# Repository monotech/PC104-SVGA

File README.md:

Schematic based on Sergey Kiselev's ISA SVGA schematic. http://www.malinov.com/Home/sergeys-projects/isa-supervga

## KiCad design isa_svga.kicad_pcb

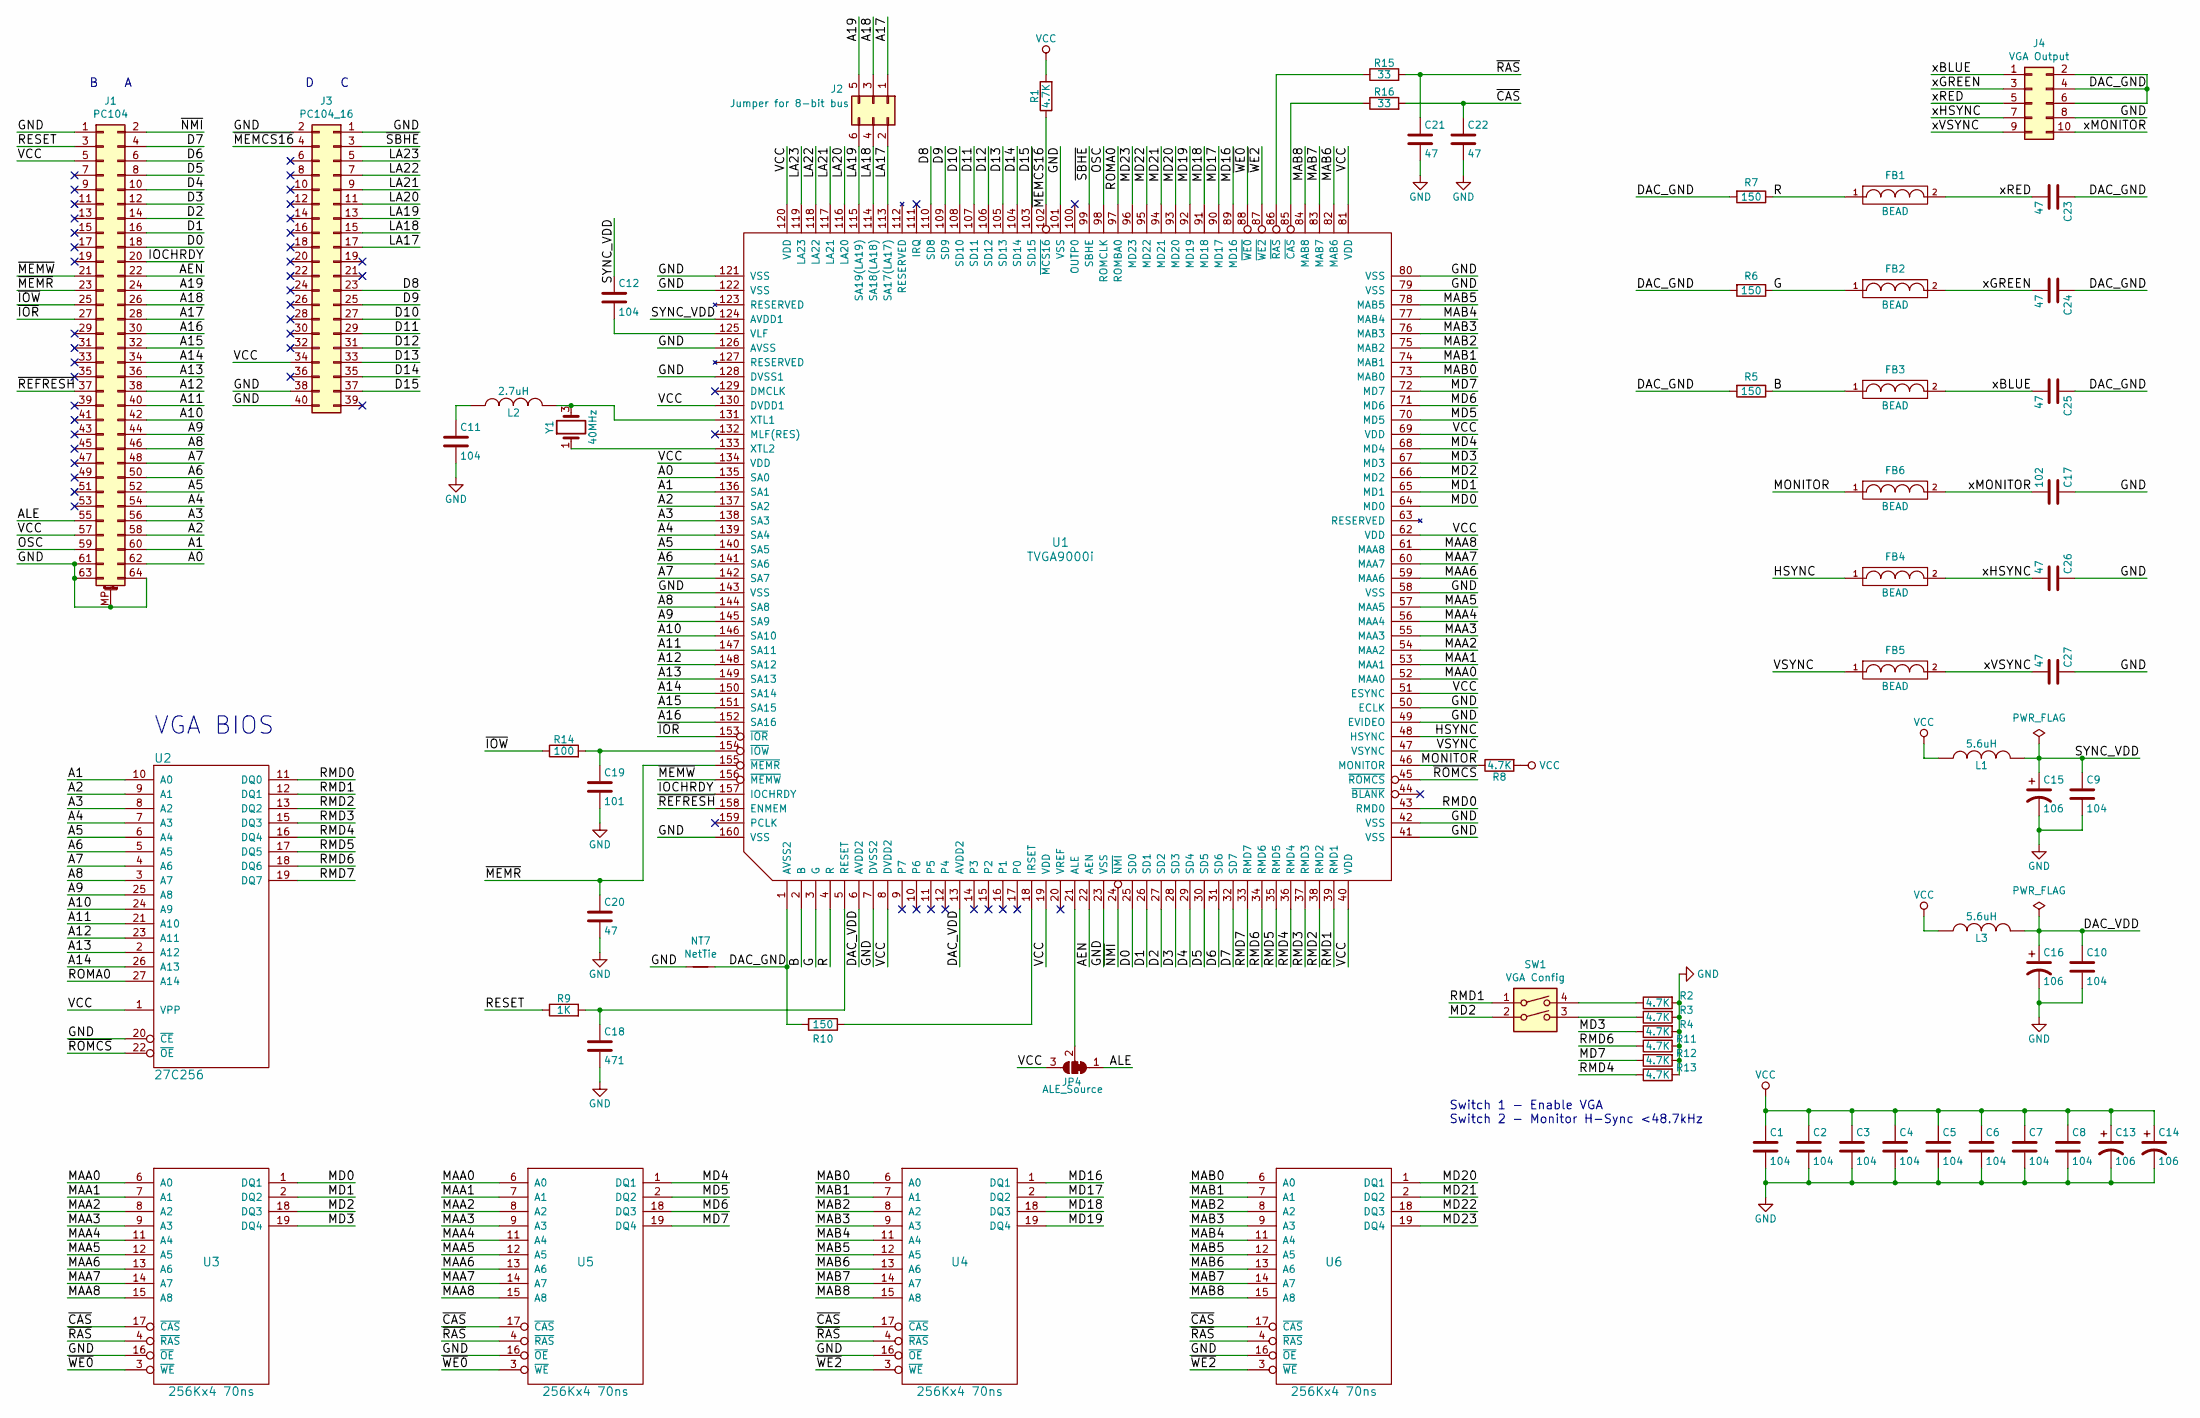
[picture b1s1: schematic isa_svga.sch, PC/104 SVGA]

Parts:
C1, C2, C3, C4, C5, C6, C7, C8, C9, C10, C11, C12: 104; C_0603_1608Metric
C13, C14, C15, C16: 106; C_0603_1608Metric
C17: 102; C_0805_2012Metric
C18: 471; C_0805_2012Metric
C19: 101; C_0805_2012Metric
C20, C21, C22, C23, C24, C25, C26, C27: 47; C_0603_1608Metric
FB1, FB2, FB3, FB4, FB5, FB6: BEAD; C_0805_2012Metric
J1: PC104; PC104_Platform
J2: Jumper for 8-bit bus; Triple-bridged-jumper
J3: PC104_16; PinSocket_2x20_P2.54mm_Vertical
J4: VGA Output; IDC-Header_2x05_P2.54mm_Horizontal
JP4: ALE_Source; SolderJumper-3_P1.3mm_Bridged12_Pad1.0x1.5mm
L1, L3: 5.6uH; C_0805_2012Metric
L2: 2.7uH; C_0805_2012Metric
NT7: NetTie; NetTie-2_SMD_Pad0.5mm
R1, R2, R3, R4, R8, R11, R12, R13: 4.7K; R_0805_2012Metric
R5, R6, R7, R10: 150; R_0805_2012Metric
R9: 1K; R_0805_2012Metric
R14: 100; R_0805_2012Metric
R15, R16: 33; R_0805_2012Metric
SW1: VGA Config; SW_DIP_SPSTx02_Slide_9.78x7.26mm_W7.62mm_P2.54mm
U1: TVGA9000i; PQFP-160_28x28mm_P0.65mm_LongPads
U2: 27C256; DIP-28_W15.24mm_Socket
U3, U4, U5, U6: 256Kx4 70ns; DIP-20_W7.62mm_Socket
Y1: 40MHz; Oscillator_SMD_Abracon_ASE-4Pin_3.2x2.5mm

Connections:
/A0: J1.62, U1.135 (SA0)
/A1: J1.60, U1.136 (SA1), U2.10 (A0)
/A2: J1.58, U1.137 (SA2), U2.9 (A1)
/A3: J1.56, U1.138 (SA3), U2.8 (A2)
/A4: J1.54, U1.139 (SA4), U2.7 (A3)
/A5: J1.52, U1.140 (SA5), U2.6 (A4)
/A6: J1.50, U1.141 (SA6), U2.5 (A5)
/A7: J1.48, U1.142 (SA7), U2.4 (A6)
/A8: J1.46, U1.144 (SA8), U2.3 (A7)
/A9: J1.44, U1.145 (SA9), U2.25 (A8)
/A10: J1.42, U1.146 (SA10), U2.24 (A9)
/A11: J1.40, U1.147 (SA11), U2.21 (A10)
/A12: J1.38, U1.148 (SA12), U2.23 (A11)
/A13: J1.36, U1.149 (SA13), U2.2 (A12)
/A14: J1.34, U1.150 (SA14), U2.26 (A13)
/A15: J1.32, U1.151 (SA15)
/A16: J1.30, U1.152 (SA16)
/A17: J1.28, J2.1
/A18: J1.26, J2.3
/A19: J1.24, J2.5
/AEN: J1.22, U1.22 (AEN)
/ALE: J1.55, JP4.1 (A)
/B: FB3.1, R5.1, U1.2 (B)
/D0: J1.18, U1.25 (SD0)
/D1: J1.16, U1.26 (SD1)
/D2: J1.14, U1.27 (SD2)
/D3: J1.12, U1.28 (SD3)
/D4: J1.10, U1.29 (SD4)
/D5: J1.8, U1.30 (SD5)
/D6: J1.6, U1.31 (SD6)
/D7: J1.4, U1.32 (SD7)
/D8: J3.23, U1.110 (SD8)
/D9: J3.25, U1.109 (SD9)
/D10: J3.27, U1.108 (SD10)
/D11: J3.29, U1.107 (SD11)
/D12: J3.31, U1.106 (SD12)
/D13: J3.33, U1.105 (SD13)
/D14: J3.35, U1.104 (SD14)
/D15: J3.37, U1.103 (SD15)
/DAC_GND: C23.1, C24.1, C25.1, J4.2, J4.4, J4.6, NT7.2, R5.2, R6.2, R7.2, R10.2, U1.1 (AVSS2)
/DAC_VDD: C10.1, C16.1, L3.2, U1.6 (AVDD2), U1.13 (AVDD2)
/G: FB2.1, R6.1, U1.3 (G)
/HSYNC: FB4.1, U1.48 (HSYNC)
/IOCHRDY: J1.20, U1.157 (IOCHRDY)
/LA17: J2.2, J3.17, U1.113 (SA17(LA17))
/LA18: J2.4, J3.15, U1.114 (SA18(LA18))
/LA19: J2.6, J3.13, U1.115 (SA19(LA19))
/LA20: J3.11, U1.116 (LA20)
/LA21: J3.9, U1.117 (LA21)
/LA22: J3.7, U1.118 (LA22)
/LA23: J3.5, U1.119 (LA23)
/MAA0: U1.52 (MAA0), U3.6 (A0), U5.6 (A0)
/MAA1: U1.53 (MAA1), U3.7 (A1), U5.7 (A1)
/MAA2: U1.54 (MAA2), U3.8 (A2), U5.8 (A2)
/MAA3: U1.55 (MAA3), U3.9 (A3), U5.9 (A3)
/MAA4: U1.56 (MAA4), U3.11 (A4), U5.11 (A4)
/MAA5: U1.57 (MAA5), U3.12 (A5), U5.12 (A5)
/MAA6: U1.59 (MAA6), U3.13 (A6), U5.13 (A6)
/MAA7: U1.60 (MAA7), U3.14 (A7), U5.14 (A7)
/MAA8: U1.61 (MAA8), U3.15 (A8), U5.15 (A8)
/MAB0: U1.73 (MAB0), U4.6 (A0), U6.6 (A0)
/MAB1: U1.74 (MAB1), U4.7 (A1), U6.7 (A1)
/MAB2: U1.75 (MAB2), U4.8 (A2), U6.8 (A2)
/MAB3: U1.76 (MAB3), U4.9 (A3), U6.9 (A3)
/MAB4: U1.77 (MAB4), U4.11 (A4), U6.11 (A4)
/MAB5: U1.78 (MAB5), U4.12 (A5), U6.12 (A5)
/MAB6: U1.82 (MAB6), U4.13 (A6), U6.13 (A6)
/MAB7: U1.83 (MAB7), U4.14 (A7), U6.14 (A7)
/MAB8: U1.84 (MAB8), U4.15 (A8), U6.15 (A8)
/MD0: U1.64 (MD0), U3.1 (DQ1)
/MD1: U1.65 (MD1), U3.2 (DQ2)
/MD2: SW1.2, U1.66 (MD2), U3.18 (DQ3)
/MD3: R4.1, U1.67 (MD3), U3.19 (DQ4)
/MD4: U1.68 (MD4), U5.1 (DQ1)
/MD5: U1.70 (MD5), U5.2 (DQ2)
/MD6: U1.71 (MD6), U5.18 (DQ3)
/MD7: R12.1, U1.72 (MD7), U5.19 (DQ4)
/MD16: U1.89 (MD16), U4.1 (DQ1)
/MD17: U1.90 (MD17), U4.2 (DQ2)
/MD18: U1.91 (MD18), U4.18 (DQ3)
/MD19: U1.92 (MD19), U4.19 (DQ4)
/MD20: U1.93 (MD20), U6.1 (DQ1)
/MD21: U1.94 (MD21), U6.2 (DQ2)
/MD22: U1.95 (MD22), U6.18 (DQ3)
/MD23: U1.96 (MD23), U6.19 (DQ4)
/MONITOR: FB6.1, R8.1, U1.46 (MONITOR)
/OSC: J1.59, U1.98 (ROMCLK)
/R: FB1.1, R7.1, U1.4 (R)
/RESET: J1.3, R9.1
/RMD0: U1.43 (RMD0), U2.11 (DQ0)
/RMD1: SW1.1, U1.39 (RMD1), U2.12 (DQ1)
/RMD2: U1.38 (RMD2), U2.13 (DQ2)
/RMD3: U1.37 (RMD3), U2.15 (DQ3)
/RMD4: R13.1, U1.36 (RMD4), U2.16 (DQ4)
/RMD5: U1.35 (RMD5), U2.17 (DQ5)
/RMD6: R11.1, U1.34 (RMD6), U2.18 (DQ6)
/RMD7: U1.33 (RMD7), U2.19 (DQ7)
/ROMA0: U1.97 (ROMBA0), U2.27 (A14)
/SYNC_VDD: C9.1, C12.1, C15.1, L1.2, U1.124 (AVDD1)
/VSYNC: FB5.1, U1.47 (VSYNC)
/xBLUE: C25.2, FB3.2, J4.1
/xGREEN: C24.2, FB2.2, J4.3
/xHSYNC: C26.2, FB4.2, J4.7
/xMONITOR: C17.2, FB6.2, J4.10
/xRED: C23.2, FB1.2, J4.5
/xVSYNC: C27.2, FB5.2, J4.9
/~CAS: C22.1, R16.2, U3.17 (~CAS), U4.17 (~CAS), U5.17 (~CAS), U6.17 (~CAS)
/~IOR: J1.27, U1.153 (~IOR)
/~IOW: J1.25, R14.1
/~MEMCS16: J3.4, R1.1, U1.102 (~MCS16)
/~MEMR: C20.1, J1.23, U1.155 (~MEMR)
/~MEMW: J1.21, U1.156 (~MEMW)
/~NMI: J1.2, U1.24 (~NMI)
/~RAS: C21.1, R15.2, U3.4 (~RAS), U4.4 (~RAS), U5.4 (~RAS), U6.4 (~RAS)
/~REFRESH: J1.37, U1.158 (ENMEM)
/~ROMCS: U1.45 (~ROMCS), U2.22 (~OE)
/~SBHE: J3.3, U1.99 (SBHE)
/~WE0: U1.88 (~WE0), U3.3 (~WE), U5.3 (~WE)
/~WE2: U1.87 (~WE2), U4.3 (~WE), U6.3 (~WE)
GND: C1.2, C2.2, C3.2, C4.2, C5.2, C6.2, C7.2, C8.2, C9.2, C10.2, C11.2, C13.2, C14.2, C15.2, C16.2, C17.1, C18.2, C19.2, C20.2, C21.2, C22.2, C26.1, C27.1, J1.1, J1.61, J1.63, J1.64, J1.MP (MountPin), J3.1, J3.2, J3.38, J3.40, J4.8, NT7.1, R2.2, R3.2, R4.2, R11.2, R12.2, R13.2, U1.7 (DVSS2), U1.23 (VSS), U1.41 (VSS), U1.42 (VSS), U1.49 (EVIDEO), U1.50 (ECLK), U1.58 (VSS), U1.79 (VSS), U1.80 (VSS), U1.101 (VSS), U1.121 (VSS), U1.122 (VSS), U1.126 (AVSS), U1.128 (DVSS1), U1.143 (VSS), U1.160 (VSS), U2.14 (GND), U2.20 (~CE), U3.16 (~OE), U3.20 (GND), U4.16 (~OE), U4.20 (GND), U5.16 (~OE), U5.20 (GND), U6.16 (~OE), U6.20 (GND)
unnamed: C11.1, L2.1
unnamed: C12.2, U1.125 (VLF)
unnamed: C18.1, R9.2, U1.5 (RESET)
unnamed: C19.1, R14.2, U1.154 (~IOW)
unnamed: JP4.2 (C), U1.21 (ALE)
unnamed: L2.2, U1.131 (XTL1), Y1.3
unnamed: R2.1, SW1.4
unnamed: R3.1, SW1.3
unnamed: R10.1, U1.18 (IRSET)
unnamed: R15.1, U1.86 (~RAS)
unnamed: R16.1, U1.85 (~CAS)
unnamed: U1.133 (XTL2), Y1.1
VCC: C1.1, C2.1, C3.1, C4.1, C5.1, C6.1, C7.1, C8.1, C13.1, C14.1, J1.5, J1.57, J3.34, JP4.3 (B), L1.1, L3.1, R1.2, R8.2, U1.8 (DVDD2), U1.19 (VDD), U1.40 (VDD), U1.51 (ESYNC), U1.62 (VDD), U1.69 (VDD), U1.81 (VDD), U1.120 (VDD), U1.130 (DVDD1), U1.134 (VDD), U2.1 (VPP), U2.28 (VCC), U3.10 (VCC), U4.10 (VCC), U5.10 (VCC), U6.10 (VCC)

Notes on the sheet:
VGA BIOS
Switch 1 - Enable VGA Switch 2 - Monitor H-Sync <48.7kHz
B A
D C

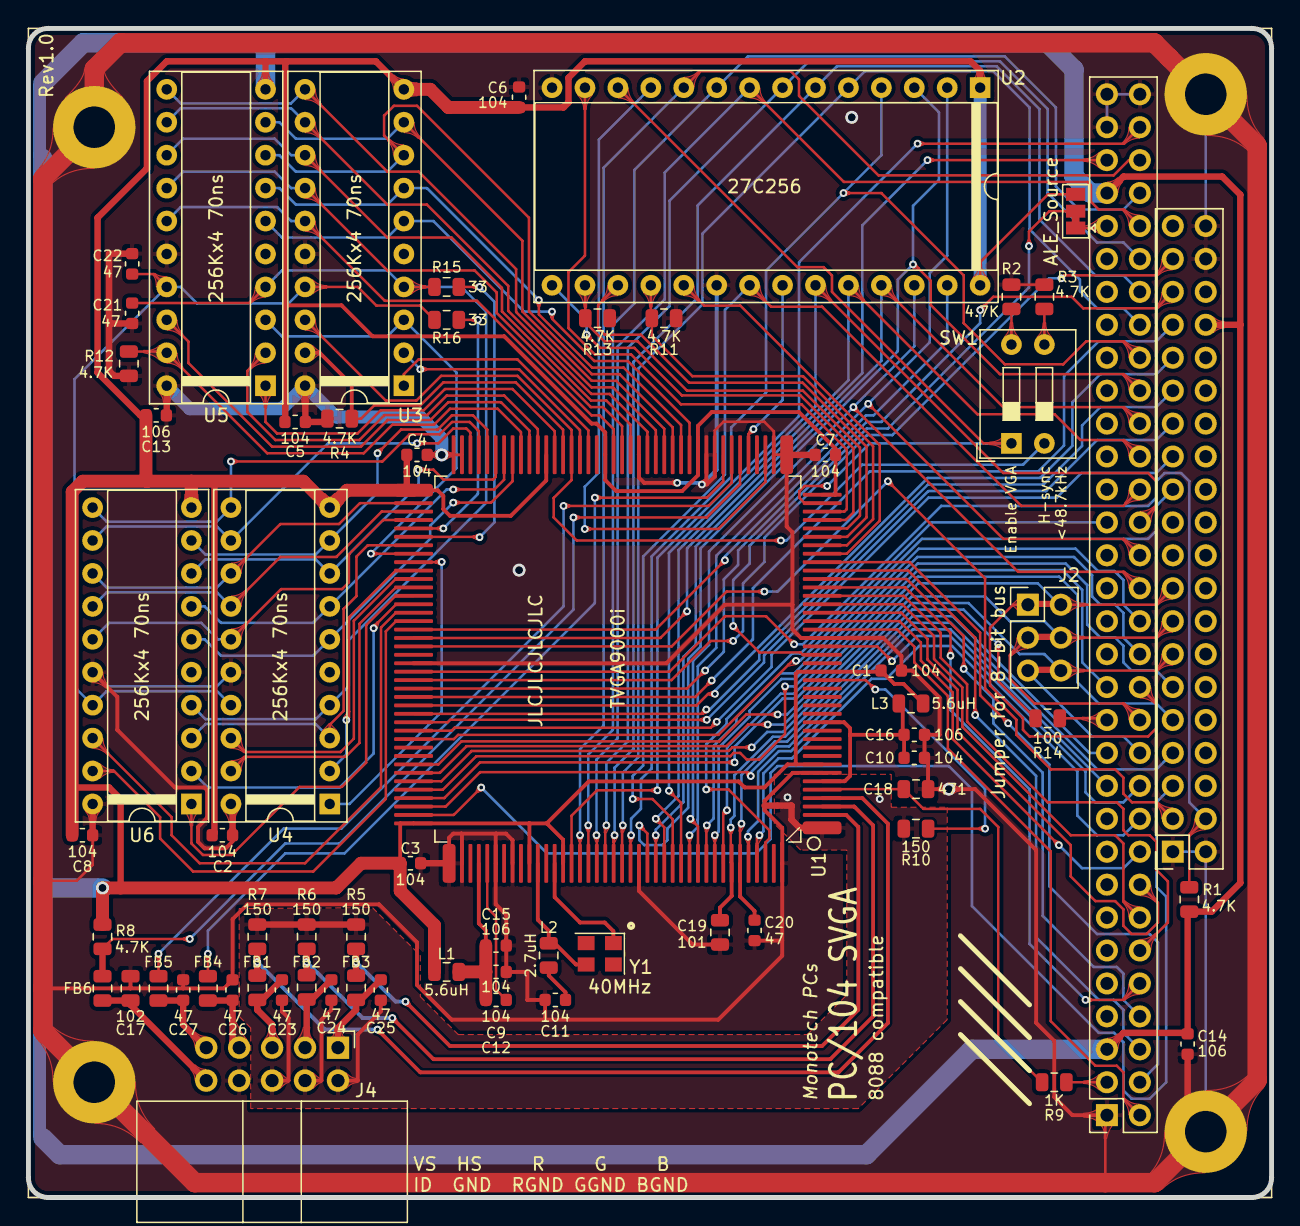
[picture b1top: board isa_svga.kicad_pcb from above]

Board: 2 copper layers, 95.9 x 90.2 mm, 66 parts (0 on the bottom side), 133 nets.
